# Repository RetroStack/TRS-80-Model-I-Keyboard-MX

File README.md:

# TRS-80 Model 1 - MX Keyboard

This project is a reimplementation of the iconic TRS-80 Model 1 computer's original keyboard. My revision replicates the functionality of the original using modern "OEM" MX-style keycaps. The entire project is available under the MIT license.

## Project Details

The project consists of multiple parts, each with its source files, an example ordering process, and consecutive assembly.

The parts are:
- [PCB](https://github.com/RetroStack/trs-80-model-i-keyboard-mx/blob/main/README.md#pcb)
- [Keycaps](https://github.com/RetroStack/trs-80-model-i-keyboard-mx/blob/main/README.md#keycaps)
- [Shield](https://github.com/RetroStack/trs-80-model-i-keyboard-mx/blob/main/README.md#shield)
- [3D printed parts (LED standoff and optional bezels)](https://github.com/RetroStack/trs-80-model-i-keyboard-mx/blob/main/README.md#3d-printed-parts)

Below is a description of the [keyboard customization](https://github.com/RetroStack/trs-80-model-i-keyboard-mx/blob/main/README.md#customizability).

See the [Assembly Guide](#assembly-guide) and [User Guide](#user-guide) below.

If you like this project, please consider [supporting it](https://github.com/RetroStack/trs-80-model-i-keyboard-mx/blob/main/README.md#support-this-project).

## PCB

The PCB has been implemented using KiCAD 7. The KiCAD project files are included in this repository.

In the "Latest" folder, you'll find the most up-to-date design files, including:

- Gerber files suitable for popular online PCB manufacturers like [PCBWay](/Latest/TRS80_Model_I_Keyboard_MX_E2_Gerber_PCBWay.zip) and [JLCPCB](/Latest/TRS80_Model_I_Keyboard_MX_E2_Gerber_JLCPCB.zip). Most manufacturers should be fine with either.
- A Bill of Materials (BOM) in [PDF](/Latest/TRS80_Model_I_Keyboard_MX_E2_BOM.pdf) format.
- The [full schematics](/Latest/TRS80_Model_I_Keyboard_MX_E2_Schematics.pdf)

### RetroStack Libraries

To work with this KiCAD project, you'll need the RetroStack libraries for KiCAD. Please [follow this link](https://www.github.com/RetroStack/KiCAD-Libraries) to access and install these libraries.

### Supported Key Switches

This PCB supports both PCB-mounted and plate-mounted MX-style key switches.

Provided holes cover both footprints on the PCB.

## Keycaps

A template of keycaps is provided that closely resembles the original keycap design.

In the "Latest" folder, you'll find the most up-to-date design files, including:

- Keycap template in [Illustrator (.ai) format](/Latest/TRS80_Model_I_Keyboard_MX_E2_Keycap_Template.ai)
- Keycap template in [SVG format](/Latest/TRS80_Model_I_Keyboard_MX_E2_Keycap_Template.svg)

These templates should work with most keycap manufacturers.

### Order Instructions - MaxKeyboard.com

Go to: [MaxKeyboard](https://maxkeyboard.com/iso-105-layout-custom-color-cherry-mx-keycap-set.html)
(If URL doesn't work anymore, select the ISO layout keycap set for MX from the store with custom prints on top.)

On the page, select the following:
- This should be for the “105” (ISO 105-key FULL SIZE)
- Select “6.0” (6.0x Unit Spacebar)
- Select “NO I have my own” (if you don’t want a keycap puller)
- Select “I will upload my print file (+US$30.00)”
- Upload the file at “Upload Your Artwork” (get the correct template to upload [here](/Latest/TRS80_Model_I_Keyboard_MX_E2_105_6.0X_TOP_PRINT_COLOR_KEY.ai))
- Add a comment “Please do not use homing keys!”

The last comment is optional but ensures that you do not have "bumps" on specific keys (e.g., the "F" and "J" key of a modern standard keyboard), which were not on the original keyboard.

NOTE: Some steps were already defined in the template file, but the website is not clear if it needs to be redefined. Just to be safe, follow the next steps as well.

What is left is the overall color design in the “DESCRIPTION” section at the bottom of the page:
- For 1. Bottom Row, select “6.0x Spacebar Row”
- For 2. Keycap Color, select the color “Black” (first) and select “All Keys”. Then, select “beige”(4th) (white is too bright and beige fits better in my opinion), and click on the keys which should be white (I marked them in the preview picture above). Select the most right “Reset” key and click “red”. The template has a few repeated keys each with a different color scheme. This gives you the opportunity later to choose the one which you like the most.
- For 3. Alphanumeric, leave everything as-is
- For 4. Modifiers, leave everything as-is
- For 5. OS Key, leave everything as-is
- For 6. Text Color, click “white” (2nd) and “All Keys”. Then select one white keycap and click “black” (1st), and select all other white keycaps. (Probably not needed, but just in case!)
- Add checkmark at “I confirm that the layout is correct”

At the end, the preview will look something like this:

It is correct that you can't see the labeling in this preview. That is provided in the template above and will not be applied to the preview you see. Some empty keys won't be used and can be discarded. They do not fit the Model 1 keyboard.

Finally, scroll up and click “Add To Cart”.

You can customize the keycap colors, but be aware that the text color is sometimes white and other times black. Here is a preview with label color for reference:

## Shield

The shield is different from the original keyboard shield as it has to accommodate the much smaller height of the MX key switches. A direct comparison to the original keyboard makes this visible:

That also required moving most components to the back of the PCB.

In the "Latest" folder, you'll find the most up-to-date design files, including:

- Shield Design in [STEP format](/Latest/TRS80_Model_I_Keyboard_MX_E2_Shield.step)
- [Flat Pattern](/Images/Shield_Flat_Pattern.png) of sheet metal design

The STEP file is accepted by most online manufacturers like [Fabworks](https://www.fabworks.com), [SendCutSend](https://sendcutsend.com), [OSHCut](https://www.oshcut.com/), or [PCBWay](https://www.pcbway.com).

The design uses the following properties which are sometimes required for the ordering process:

- Suggested Material: Steel G90 (SendCutSend), Steel 1008 (Fabworks)
- Thickness: 1.22mm (0.048")
- K Factor: 0.46
- Bend Radius: 0.762
- Finish: Matte Black

### Order Instructions - [Fabworks](https://www.fabworks.com)

Go to [Fabworks](https://www.fabworks.com) and drop the [STEP file](/Latest/TRS80_Model_I_Keyboard_MX_E2_Shield.step) into the upload section (or select it by clicking it).

This will open up a new page and show a small preview of the shield. 

- Select the material "Steel 1008".
- Set thickness to 0.048" or 1.22mm.
- Select "Matte Black" as finish.
- (optionally) Modify the quantity

Click on "Checkout".

NOTE: The original shield has a thickness of 1.5mm. However, if you select 1.5mm and the paint of the finish is added, the thickness will increase, and the key switches won't fit anymore (or at least will not click in). Additionally, the design is for 1.22mm. Changing the thickness to another value will change the position of the mounting holes slightly. Small variations, however, should not be problematic.

## 3D Printed Parts

In the "Latest" folder, you'll find the most up-to-date design files, including:

- LED Standoff in [STL format](/Latest/TRS80_Model_I_Keyboard_MX_E2_LED_StandOff.stl)
- Bezel with Numpad in [STL format](/Latest/TRS80_Model_I_Keyboard_MX_E2_Bezel_with_NumPad.stl)
- Bezel without Numpad in [STL format](/Latest/TRS80_Model_I_Keyboard_MX_E2_Bezel.stl)

### LED Standoff

The LED standoff needed to be redesigned from the original since the PCB is much closer to the shield, requiring a reduction in size.

This is an optional item and not necessarily required. However, without it, you might struggle to solder the LED to the correct distance to surface the bezel:

Additionally, without the standoff, you might bump into the LED as it extends above the PCB, and this will hinder you from aligning the bezel and case over the keyboard until you bend it to the right position again.

### Bezels

I've also provided two additional bezels in addition to the [original](https://github.com/RetroStack/TRS-80-Model-I-Parts/tree/main/Keyboard_Bezel) to help cover the two keys in case you do not want to add them.

An example can be seen here:

### Order Instruction - [JLC3DP](https://www.jlcpcb.com) (service of JLCPCB)

You can print them yourself, but most likely you do not have such a large printer. You can order them online. What follows are instructions for JLC3DP, which I've had good experiences with. Additionally, they take care of sanding and finishing.

- Go to [JLC3DP](https://www.jlcpcb.com).
- Click the "Quote Now" button under the "3D Printing" image.
- Click the "Add 3D file" and select the STL file provided above.

A few options appear. In either case, I always selected "SLA(Resin)" for the technology, which has a very smooth surface.

You can leave "LEDO 6060 Resin" for the LED standoff. That resin is white, and the standoff is hidden anyway inside the keyboard. It is also the cheapest option.
For the bezel, however, I would choose the "Black Resin" option. It is a bit more expensive, but it will reduce post-processing for you as you probably do not want a white bezel.

Leave all other options as-is.

You still have to select a "Product Description". Apparently, this is some customs requirement. I've selected for both "Office Appliances and Accessories" and "Keyboard Enclosure".

You can then hit "Save to Cart" and checkout.

By default, they will review your designs and send you an email to pay within a few hours. Simply go back to your order page (after you've created an account) and select "Pay".

NOTE: Most of the time, however, they will also send you an email to confirm that you want to assume the risk of ordering the design as-is as they are too long and may deform during production or have parts which are too thin. I've always accepted the risk and never had any trouble.

## Customizability

Since there was an opportunity to improve upon the keyboard, I provided various ways to optionally customize your keyboard.

### Additional Keys

Modern keyboards generally use 6 units (6u) wide spacebars (or similar short sizes) instead of the 8 units (8u) the original Model I keyboard used. This replacement keyboard comes with a 6 units wide spacebar, which means that there is additional space next to the spacebar for two additional keys to fill the gap of the original keyboard bezel.

Any key can be [mapped](/Images/Keyboard_Mapper.png) to these two additional keys by selecting the row and column:

On the underside, you can add DIP switches (or simply use jumpers) to select the row and column:

NOTE: Make sure to only select one per DIP-switch row. If you select more than one, the keyboard will behave erratically. However, it will also not break anything.

### Remap other Keys

You can also remap the BREAK and CLEAR keys to anything you want:

### Add Reset Key

To emulate a popular Model 3 & 4 keyboard feature, the ability to add a reset key is provided:

Simply add a jumper to the keyboard:

Then, connect to a via close to the reset circuity on the main board:

On the back of the board, select Row 9 and Column 9 as shown in the [mapper](/Images/Keyboard_Mapper.png):

### Keycap Variations

As each keycap set consists of 105 keys. The basic keyboard without a numpad requires only 53 keys, while with a numpad, it needs 65 keys. Even with the additional 2 keys, we need at most 67 keys. There are 38 keys left (minus some unused key sizes and shapes), which can be duplicated. I've provided a few variations of keycaps in different colors, but also custom prints (like the CTRL key for "Electric Pencil"):

This provides a couple of variations (and more):

## Assembly Guide

1. **Solder Components on PCB**
* Begin by soldering all components on the back side of the PCB. This includes:
  * **Integrated Circuits (ICs)**
    * Match notch on PCB with notch on IC
    * Z1 & Z2 are the 74LS05s, while Z3 & Z4 are the 74LS368s
  * **Capacitors**
    * Both are the same. No orientation needed.
  * **LED resistor**
  * **Resistor network**
    * Match dot on the side of the resistor network with the square on one end of the footprint on the PCB.
  * **Right-angle header**
    * Solder this outward from the keyboard PCB
* Ensure all components are securely soldered and correctly oriented.
2. (Optional) **Install DIP Switches**
  * DIP Switches for additional keys:
    * There are four DIP switches located near the spacebar at the bottom of the PCB. These switches are for configuring the two additional keys next to the spacebar.
    * This step is optional and only necessary if you intend to use these additional keys.
    * Alternatively, you can use jumper cables instead of the DIP switches to set a fixed configuration.
  * DIP Switches for key remapping:
    * Four more DIP switches are located near the CLEAR and BREAK keys at the top right (from the back) of the PCB. These are used to remap these keys.
    * By default, these keys are set to their original mapping. To change the mapping, you need to cut the jumpers next to the DIP switches.
    * This is also optional and not required for standard use.
3. **Solder the LED**
  * On the front side of the PCB, solder the LED into place.
  * Use the stand-off provided to ensure proper clearance from PCB and to align it with the case later on. Align the flat edge of the stand-off with the LED and the graphic on the PCB.
  * Install the LED before adding the shield, as it will be difficult to place the stand-off after the shield is attached.
4. **Install Keyswitches in Corners**
  * Begin by adding keyswitches to all four corners of the keyboard (do not install the spacebar keyswitches yet).
  * Ensure keyswitches are installed in the correct orientation. Note that some keyswitches, such as those for SHIFT keys, need to be oriented differently.
  * Additionally, place a central keyswitch at the H position for extra support. If you are installing a numpad, add keyswitches to all four corners of the numpad.
  * Verify that all pins of the keyswitches are straight to facilitate proper alignment in the next steps.
5. **Align and Solder Keyswitches to Shield**
  * Place the shield with the keyswitches lying flat on a table, with the bottom of the shield facing you.
  * Carefully align the PCB with the keyswitches and lay it flat into the back of the shield.
  * Ensure all keyswitch pins are properly extending out of the PCB.
  * Once alignment is confirmed, solder the keyswitches in place.
6. **Install Remaining Keyswitches**
  * Flip the shield with the attached PCB and proceed to install the remaining keyswitches.
  * For each keyswitch, ensure that the pins are straight and insert the keyswitch vertically into the shield. Push down to lock it into place.
  * Continue this process for all keyswitches, except the spacebar. Remember that some keyswitches may require a different orientation.
7. **Solder All Keyswitches**
  * With all keyswitches in place (except the spacebar), solder them onto the PCB.
8. **Install Spacebar Keyswitches**
  * Install the keyswitches for the spacebar but keep them unsoldered for now.
  * Typically, two outer keyswitches are sufficient. Adding a center keyswitch increases resistance and might affect the feel, so this is a matter of personal preference.
  * The PCB has elongated footprints for the outer spacebar keyswitches to accommodate various spacebar styles.
  * Clip the spacebar keycap (from the keycaps box) into the outer keyswitches (and center if used). Adjust the outer keyswitches if needed to ensure a proper fit.
9. **Test and Adjust Spacebar**
  * Test the spacebar keycap. Check if it presses smoothly or gets stuck.
  * If the spacebar is resisting or sticking, adjust the position of the outer keyswitches until the spacebar moves freely. Usually moving them outward helps.
10. **Solder Spacebar Keyswitches**
  * With the spacebar keycap still attached, flip the keyboard and solder the spacebar keyswitches in place.
  * Keeping the keycap attached ensures that the keyswitches do not shift before soldering.
11. **Add Keycaps**
  * Install all the keycaps onto the keyswitches.
  * The keycap set comes with various color schemes for specific keys. For an authentic look, use white keycaps for ENTER keys and black for all other keys.
  * You can always change the keycaps later if desired.
12. (Optional) **Adjust Metal Shield**
  * Some metal shields may not fit perfectly because they aren’t always bent exactly 90 degrees. Often, they are slightly too wide, making it difficult to fit them into the case without putting excessive strain on the posts.
  * To adjust the fit, hold the assembled keyboard in front of you, angled downward against your body. The metal tabs with the mounting holes should be positioned on the left and right sides of you.
  * Gently press the two metal tabs at the front and back of the shield together, slightly bending them inwards.
    * Apply even pressure on both sides to avoid bending one side more than the other. Uneven bending will prevent the keyboard from fitting properly into the case.
    * __Don’t overbend__ the shield, as this is much harder to correct afterward.
  * Repeat this process for each horizontal section where the holes are located (2 sections in total).
  * After each adjustment, check how the shield fits in the case. It should gradually get closer to the perfect fit with each adjustment.

## User Guide

### Installation

If your old keyboard already uses a header, simply disconnect the old ribbon cable from the computer and/or keyboard, remove the old keyboard from the case, and attach the new cable to the mainboard. I prefer using a 40-pin IDC cable which can be quite short. Ensure that the red side of the IDC ribbon cable faces pin 1 or 2 on both the keyboard and mainboard. Since the IDC cable has two rows per connector, use only one side of the connector—typically the row closest to the notch.

If you use the wrong row, nothing will break, and the keyboard will simply not work. A good way to check if the connection was made correctly is that the LED lights up when the computer is turned on.

### Key Mapping

This replacement keyboard includes optional DIP switches on the bottom, allowing you to reconfigure the additional keys next to the spacebar, as well as the BREAK and CLEAR keys. By default, the BREAK and CLEAR keys are mapped to their original functionality and working as expected. You can remap these keys and the additional keys next to the spacebar using the [MX Keyboard Mapper page](/Latest/TRS80_Model_I_Keyboard_MX_E2_Mapper.pdf) in the Latest directory, which includes a full overview of the M1 keyboard matrix.

**Example**: To remap a key to "T," set the **R**(ow) DIP switch to 3 (R3) and the **C**(olumn) DIP switch to 5 (C5).

**NOTE**: Never switch more than one DIP switch per DIP switch row, as it will result in unexpected key mappings across the keyboard, affecting keys that are completely unrelated due to the matrix. If your keyboard reacts erratically, check to ensure you haven't inadvertently switched more than one key in each DIP switch row.

### Installing the Right-Angle Header on the Mainboard

If your mainboard still uses the foil-type connector, it needs to be removed, as these are prone to failure. The included right-angle header should be installed in its place. 

#### To remove the foil-type ribbon cable

Cut the ribbon cable close to the mainboard. On the small piece left on the mainboard, make a cut between each wire to separate them. This simplifies the removal of each individual wire, reducing strain on neighboring pads and minimizing the risk of lifting pads off the board. After removing all wires, use a solder wick to clean the pads, being careful not to overheat them. Once the pads are clean, solder the right-angle header inwards, ensuring it fits within the case.

### Installing the RESET Key

To enable the RESET function, connect the jumper wire between the keyboard and the mainboard. Use a Dupont-style wire with a female connector on one side for easy detachment later on. You don't want to solder the mainboard and keyboard permanently together. Solder one end to the marked via on the mainboard and connect the other end to a 1-pin header on the keyboard's RST pad.
To configure the mapping, set the key to **R**(ow) 9 (R9) and **C**(olumn) 9 (C9), and replace the keycap with the red RESET key. This setup allows the keyboard’s RESET key to function as the mainboard's reset button.

## Main TRS-80 Model 1 Repository

For additional resources related to the TRS-80 Model 1, be sure to check out the central page for the TRS-80 Model 1 on RetroStack. You can find it [here](https://www.github.com/RetroStack/TRS-80-Model-I).

## Support this Project

RetroStack is passionate about exploring and preserving the legacy of older computer systems. My work involves creating detailed documentation and videos to share the knowledge. I am also dedicated to reviving these classic systems by reimplementing them and offering replacement parts at no cost. If you're keen on supporting this unique project, I invite you to visit my [Patreon page](https://www.patreon.com/RetroStack). Your support would be immensely valuable and greatly appreciated!

## License

This project is licensed under the MIT License - see the [LICENSE](LICENSE) file for details.

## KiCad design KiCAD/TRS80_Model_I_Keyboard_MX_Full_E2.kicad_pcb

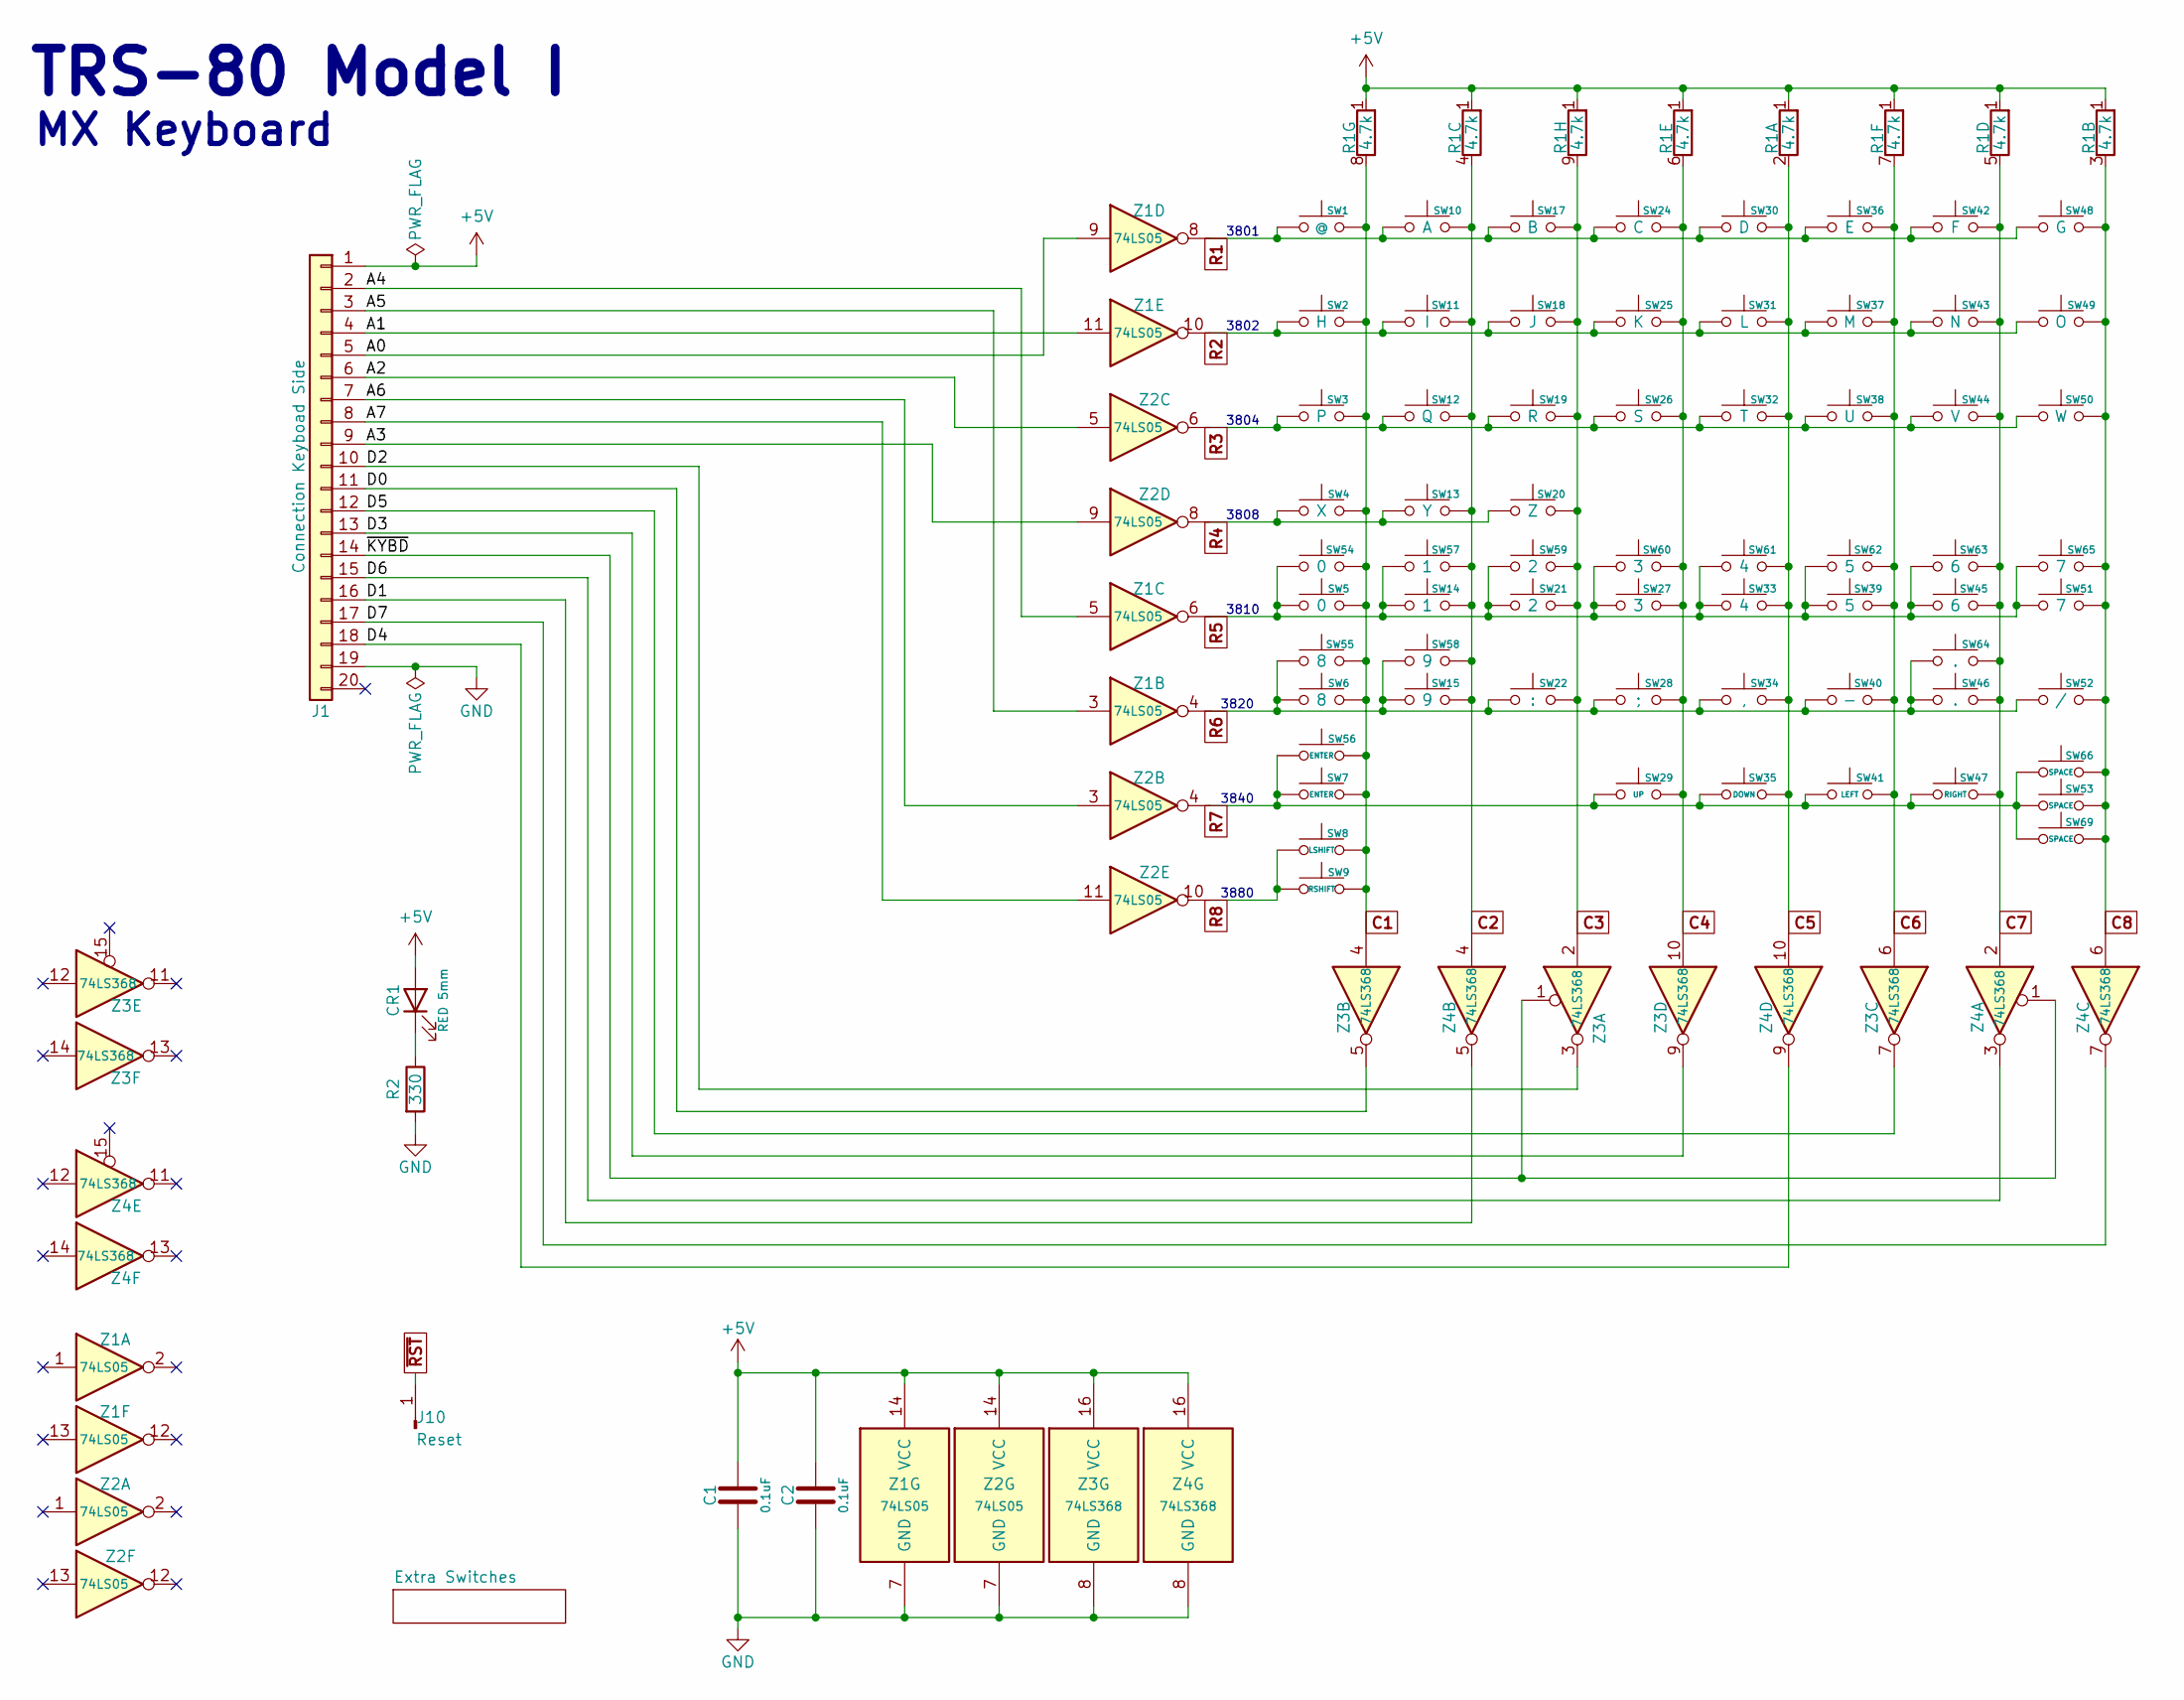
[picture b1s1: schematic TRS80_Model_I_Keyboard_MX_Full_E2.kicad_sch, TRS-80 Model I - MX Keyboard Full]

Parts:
C1, C2: 0.1uF; TRS80_Model_I_C_Disc_9.5L_4W_6P_Small
CR1: RED 5mm; LED_D5.0mm
J1: Connection Keyboad Side; PinHeader_1x20_P2.54mm_Vertical
J10: Reset; PinHeader_1x01_P2.54mm_Vertical
R1: 4.7k; R_Array_SIP9
R2: 330; TRS80_Model_I_R_0.25W
SW1: @; SW_Cherry_MX_1.00u_PCB
SW2: H; SW_Cherry_MX_1.00u_PCB
SW3: P; SW_Cherry_MX_1.00u_PCB
SW4: X; SW_Cherry_MX_1.00u_PCB
SW5, SW54: 0; SW_Cherry_MX_1.00u_PCB
SW6, SW55: 8; SW_Cherry_MX_1.00u_PCB
SW7, SW56: ENTER; SW_Cherry_MX_1.00u_PCB
SW8: LSHIFT; SW_Cherry_MX_1.00u_PCB
SW9: RSHIFT; SW_Cherry_MX_1.00u_PCB
SW10: A; SW_Cherry_MX_1.00u_PCB
SW11: I; SW_Cherry_MX_1.00u_PCB
SW12: Q; SW_Cherry_MX_1.00u_PCB
SW13: Y; SW_Cherry_MX_1.00u_PCB
SW14, SW57: 1; SW_Cherry_MX_1.00u_PCB
SW15, SW58: 9; SW_Cherry_MX_1.00u_PCB
SW17: B; SW_Cherry_MX_1.00u_PCB
SW18: J; SW_Cherry_MX_1.00u_PCB
SW19: R; SW_Cherry_MX_1.00u_PCB
SW20: Z; SW_Cherry_MX_1.00u_PCB
SW21, SW59: 2; SW_Cherry_MX_1.00u_PCB
SW22: :; SW_Cherry_MX_1.00u_PCB
SW24: C; SW_Cherry_MX_1.00u_PCB
SW25: K; SW_Cherry_MX_1.00u_PCB
SW26: S; SW_Cherry_MX_1.00u_PCB
SW27, SW60: 3; SW_Cherry_MX_1.00u_PCB
SW28: ;; SW_Cherry_MX_1.00u_PCB
SW29: UP; SW_Cherry_MX_1.00u_PCB
SW30: D; SW_Cherry_MX_1.00u_PCB
SW31: L; SW_Cherry_MX_1.00u_PCB
SW32: T; SW_Cherry_MX_1.00u_PCB
SW33, SW61: 4; SW_Cherry_MX_1.00u_PCB
SW34: ,; SW_Cherry_MX_1.00u_PCB
SW35: DOWN; SW_Cherry_MX_1.00u_PCB
SW36: E; SW_Cherry_MX_1.00u_PCB
SW37: M; SW_Cherry_MX_1.00u_PCB
SW38: U; SW_Cherry_MX_1.00u_PCB
SW39, SW62: 5; SW_Cherry_MX_1.00u_PCB
SW40: -; SW_Cherry_MX_1.00u_PCB
SW41: LEFT; SW_Cherry_MX_1.00u_PCB
SW42: F; SW_Cherry_MX_1.00u_PCB
SW43: N; SW_Cherry_MX_1.00u_PCB
SW44: V; SW_Cherry_MX_1.00u_PCB
SW45, SW63: 6; SW_Cherry_MX_1.00u_PCB
SW46, SW64: .; SW_Cherry_MX_1.00u_PCB
SW47: RIGHT; SW_Cherry_MX_1.00u_PCB
SW48: G; SW_Cherry_MX_1.00u_PCB
SW49: O; SW_Cherry_MX_1.00u_PCB
SW50: W; SW_Cherry_MX_1.00u_PCB
SW51, SW65: 7; SW_Cherry_MX_1.00u_PCB
SW52: /; SW_Cherry_MX_1.00u_PCB
SW53, SW66: SPACE; SW_Cherry_MX_1.00u_PCB_Spacebar_Universal
SW69: SPACE; SW_Cherry_MX_1.00u_PCB
Z1, Z2: 74LS05; TRS80_Model_I_DIP14
Z3, Z4: 74LS368; TRS80_Model_I_DIP16

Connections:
+5V: C1.1, C2.1, CR1.2 (A), J1.1, R1.1 (R1), Z1.14 (VCC), Z2.14 (VCC), Z3.16 (VCC), Z4.16 (VCC)
/A0: J1.5, Z1.9
/A1: J1.4, Z1.11
/A2: J1.6, Z2.5
/A3: J1.9, Z2.9
/A4: J1.2, Z1.5
/A5: J1.3, Z1.3
/A6: J1.7, Z2.3
/A7: J1.8, Z2.11
/D0: J1.11, Z3.5
/D1: J1.16, Z4.5
/D2: J1.10, Z3.3
/D3: J1.13, Z3.9
/D4: J1.18, Z4.9
/D5: J1.12, Z3.7
/D6: J1.15, Z4.3
/D7: J1.17, Z4.7
/~KYBD: J1.14, Z3.1, Z4.1
C1: R1.8 (R7.2), SW1.1, SW2.1, SW3.1, SW4.2, SW5.2, SW6.2, SW7.1, SW8.1, SW9.2, SW54.1, SW55.1, SW56.2, Z3.4; also elsewhere on the board
C2: R1.4 (R3.2), SW10.2, SW11.1, SW12.1, SW13.1, SW14.1, SW15.1, SW57.1, SW58.1, Z4.4; also elsewhere on the board
C3: R1.9 (R8.2), SW17.1, SW18.1, SW19.2, SW20.1, SW21.2, SW22.2, SW59.2, Z3.2; also elsewhere on the board
C4: R1.6 (R5.2), SW24.1, SW25.2, SW26.2, SW27.1, SW28.2, SW29.2, SW60.1, Z3.10; also elsewhere on the board
C5: R1.2 (R1.2), SW30.2, SW31.1, SW32.2, SW33.1, SW34.2, SW35.1, SW61.1, Z4.10; also elsewhere on the board
C6: R1.7 (R6.2), SW36.2, SW37.2, SW38.2, SW39.1, SW40.1, SW41.2, SW62.1, Z3.6; also elsewhere on the board
C7: R1.5 (R4.2), SW42.2, SW43.2, SW44.2, SW45.1, SW46.2, SW47.1, SW63.1, SW64.2, Z4.2; also elsewhere on the board
C8: R1.3 (R2.2), SW48.1, SW49.2, SW50.1, SW51.1, SW52.1, SW53.1, SW65.2, SW66.1, SW69.1, Z4.6; also elsewhere on the board
GND: C1.2, C2.2, J1.19, R2.2, Z1.7 (GND), Z2.7 (GND), Z3.8 (GND), Z4.8 (GND); also elsewhere on the board
unnamed: CR1.1 (K), R2.1
R1: SW1.2, SW10.1, SW17.2, SW24.2, SW30.1, SW36.1, SW42.1, SW48.2, Z1.8; also elsewhere on the board
R2: SW2.2, SW11.2, SW18.2, SW25.1, SW31.2, SW37.1, SW43.1, SW49.1, Z1.10; also elsewhere on the board
R3: SW3.2, SW12.2, SW19.1, SW26.1, SW32.1, SW38.1, SW44.1, SW50.2, Z2.6; also elsewhere on the board
R4: SW4.1, SW13.2, SW20.2, Z2.8; also elsewhere on the board
R5: SW5.1, SW14.2, SW21.1, SW27.2, SW33.2, SW39.2, SW45.2, SW51.2, SW54.2, SW57.2, SW59.1, SW60.2, SW61.2, SW62.2, SW63.2, SW65.1, Z1.6; also elsewhere on the board
R6: SW6.1, SW15.2, SW22.1, SW28.1, SW34.1, SW40.2, SW46.1, SW52.2, SW55.2, SW58.2, SW64.1, Z1.4; also elsewhere on the board
R7: SW7.2, SW29.1, SW35.2, SW41.1, SW47.2, SW53.2, SW56.1, SW66.2, SW69.2, Z2.4; also elsewhere on the board
R8: SW8.2, SW9.1, Z2.10; also elsewhere on the board
~RST: J10.1; also elsewhere on the board

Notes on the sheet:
3804
3880
TRS-80 Model I
MX Keyboard
3808
3810
3820
3802
3801
3840

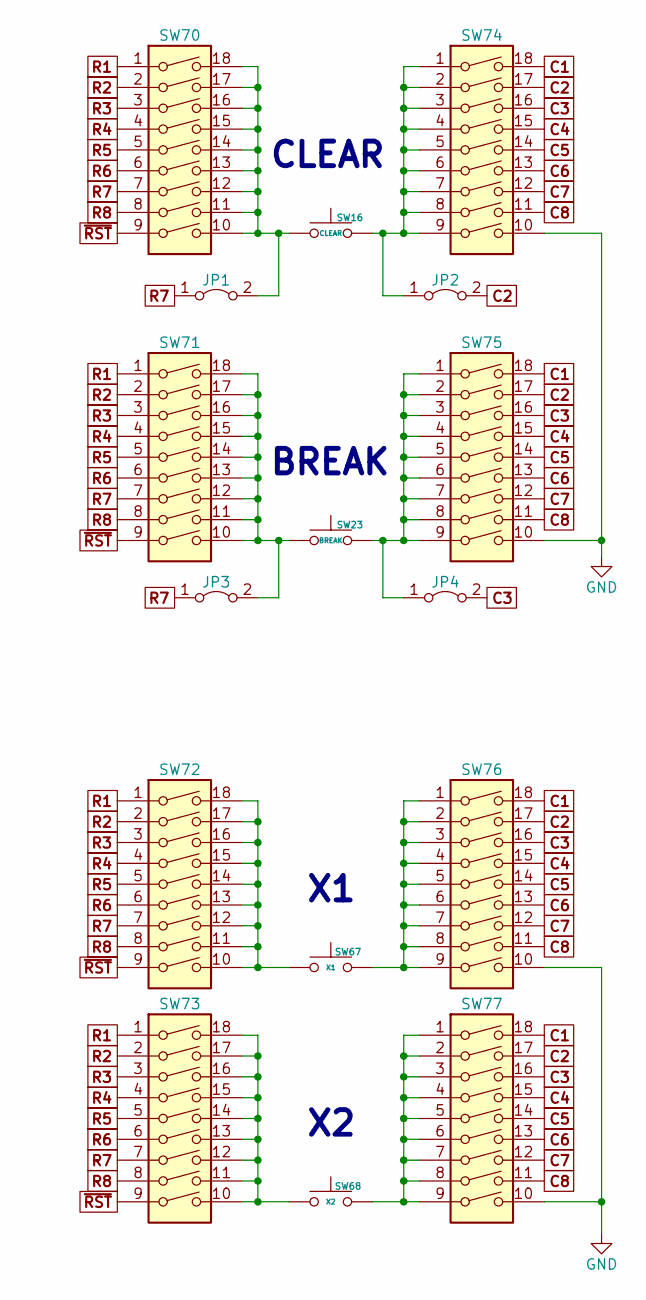
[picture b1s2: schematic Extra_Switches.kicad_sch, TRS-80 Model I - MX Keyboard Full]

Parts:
JP1, JP2, JP3, JP4: Jumper_2_Bridged; SolderJumper-2_P1.3mm_Bridged_RoundedPad1.0x1.5mm
SW16: CLEAR; SW_Cherry_MX_1.00u_PCB
SW23: BREAK; SW_Cherry_MX_1.00u_PCB
SW67: X1; SW_Cherry_MX_1.00u_PCB
SW68: X2; SW_Cherry_MX_1.00u_PCB
SW70, SW71, SW72, SW73, SW74, SW75, SW76, SW77: SW_DIP_x09; DIP-18_W7.62mm

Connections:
C1: SW74.18, SW75.18, SW76.18, SW77.18; also elsewhere on the board
C2: JP2.2 (B), SW74.17, SW75.17, SW76.17, SW77.17; also elsewhere on the board
C3: JP4.2 (B), SW74.16, SW75.16, SW76.16, SW77.16; also elsewhere on the board
C4: SW74.15, SW75.15, SW76.15, SW77.15; also elsewhere on the board
C5: SW74.14, SW75.14, SW76.14, SW77.14; also elsewhere on the board
C6: SW74.13, SW75.13, SW76.13, SW77.13; also elsewhere on the board
C7: SW74.12, SW75.12, SW76.12, SW77.12; also elsewhere on the board
C8: SW74.11, SW75.11, SW76.11, SW77.11; also elsewhere on the board
GND: SW74.10, SW75.10, SW76.10, SW77.10; also elsewhere on the board
unnamed: JP1.2 (B), SW16.1, SW70.10, SW70.11, SW70.12, SW70.13, SW70.14, SW70.15, SW70.16, SW70.17, SW70.18
unnamed: JP2.1 (A), SW16.2, SW74.1, SW74.2, SW74.3, SW74.4, SW74.5, SW74.6, SW74.7, SW74.8, SW74.9
unnamed: JP3.2 (B), SW23.1, SW71.10, SW71.11, SW71.12, SW71.13, SW71.14, SW71.15, SW71.16, SW71.17, SW71.18
unnamed: JP4.1 (A), SW23.2, SW75.1, SW75.2, SW75.3, SW75.4, SW75.5, SW75.6, SW75.7, SW75.8, SW75.9
unnamed: SW67.1, SW76.1, SW76.2, SW76.3, SW76.4, SW76.5, SW76.6, SW76.7, SW76.8, SW76.9
unnamed: SW67.2, SW72.10, SW72.11, SW72.12, SW72.13, SW72.14, SW72.15, SW72.16, SW72.17, SW72.18
unnamed: SW68.1, SW77.1, SW77.2, SW77.3, SW77.4, SW77.5, SW77.6, SW77.7, SW77.8, SW77.9
unnamed: SW68.2, SW73.10, SW73.11, SW73.12, SW73.13, SW73.14, SW73.15, SW73.16, SW73.17, SW73.18
R1: SW70.1, SW71.1, SW72.1, SW73.1; also elsewhere on the board
R2: SW70.2, SW71.2, SW72.2, SW73.2; also elsewhere on the board
R3: SW70.3, SW71.3, SW72.3, SW73.3; also elsewhere on the board
R4: SW70.4, SW71.4, SW72.4, SW73.4; also elsewhere on the board
R5: SW70.5, SW71.5, SW72.5, SW73.5; also elsewhere on the board
R6: SW70.6, SW71.6, SW72.6, SW73.6; also elsewhere on the board
R7: JP1.1 (A), JP3.1 (A), SW70.7, SW71.7, SW72.7, SW73.7; also elsewhere on the board
R8: SW70.8, SW71.8, SW72.8, SW73.8; also elsewhere on the board
~RST: SW70.9, SW71.9, SW72.9, SW73.9; also elsewhere on the board

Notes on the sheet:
BREAK
CLEAR

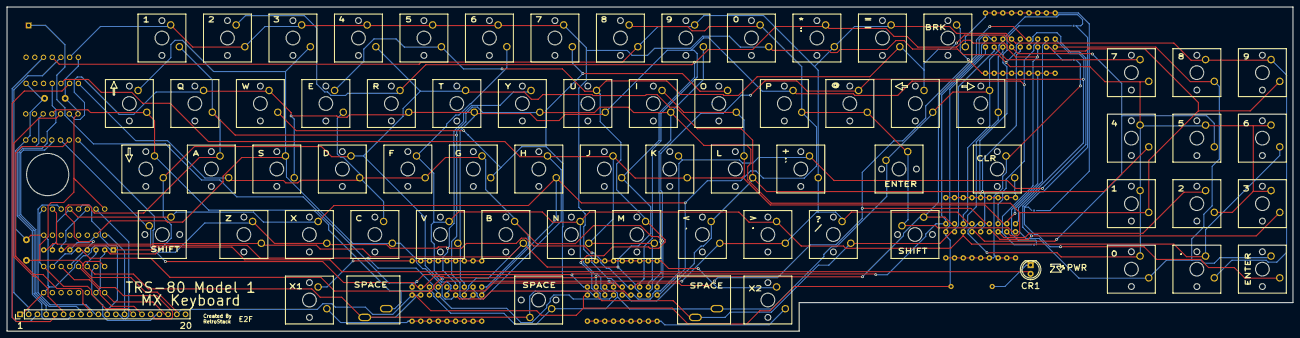
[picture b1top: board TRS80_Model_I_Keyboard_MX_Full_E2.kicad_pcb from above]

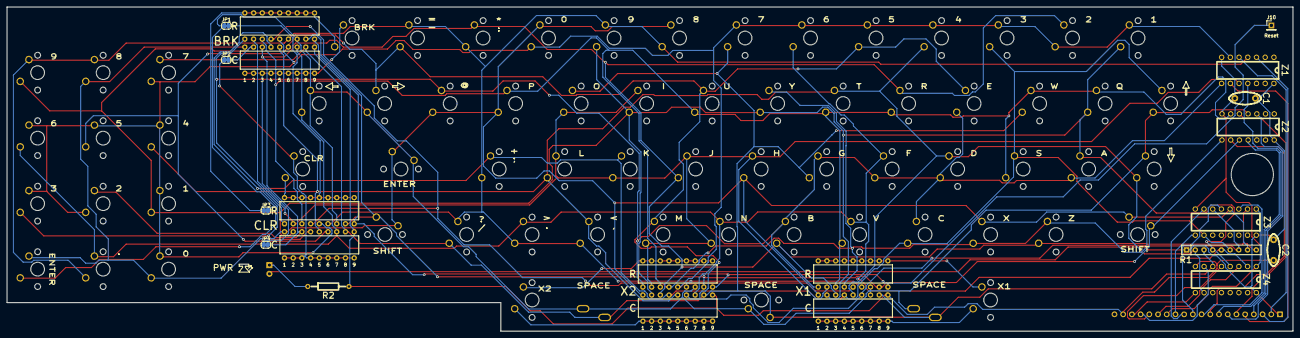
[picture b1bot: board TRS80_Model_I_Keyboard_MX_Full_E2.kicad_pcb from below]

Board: 2 copper layers, 375.0 x 94.5 mm, 92 parts (21 on the bottom side), 45 nets.

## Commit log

2024-04-25 More images
2024-05-05 Add default STEP file
2024-05-20 Update LICENSE
2024-06-26 E2E changes
2024-08-23 E2F version
2024-09-07 Add docs images
2024-09-07 Smaller images
2025-09-02 Updated link and description for Maxkeyboards website
2025-09-02 Fix MaxKeyboard URL in order instructions

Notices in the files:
README.md:
License:
This project is licensed under the MIT License - see the [LICENSE](LICENSE) file for details.
